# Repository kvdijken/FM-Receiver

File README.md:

# FM Receiver

In this project you will find my home built FM receiver. The goal is to create a receiver with discrete components only, no integrated circuits. It delivers line level audio. It only needs an additional audio amplifier to be able to hear your favorite radio station from the speakers.

Performance is very good. I receive all FM radio stations with great clarity. Its sensitivity is 11𝜇V.

It lets you dial into preprogrammed radio stations, or to select frequencies yourself. Also you can change some internal receiver parameters such as intermediate frequencies and lowside/highside injection. 

The user interface runs on an Arduino Nano 328P. The receiver itself is built off discrete parts, no integrated parts are used.

In this project you will find
* Arduino source code of the digital section (in folder 'firmware/FM Radio 5.8')
* Kicad project with the schematic and pcb layout of the analog section (in folder 'hardware')
* documentation (in folder 'documentation')
* a Python project to model differential pair amplifiers (in folder 'IF Amplifier')
* some photos of my implementation
* measurements I have done on this receiver (in folder 'measurements').

In this project you will not find the schematic for the digital section yet. I will still have to create this schematic. The digital section is not complicated however. It consists of an Arduino Nano, three pushbuttons, one LED, 1 rotary encoder, one display and one Adafruit Si5351 breakout board. From the Arduino sourcecode you should be able to discover the wiring. The Si5351 delivers the two local oscillator frequencies which are needed for the receiver.

Keep in mind that the schematic, and the pcb which is derived from the schematic contain an serious error. I kept this error in the schematic, to keep the schematic and pcb design in sync. The error is described in the documentation. Also is described how to work around the error, which is quite simple. You can still use the pcb design, even with this bug. In the next version of this receiver this error will be solved.

In the next few weeks, months, my main focus will be on measurements on the receiver. I will try to characterise the receiver as well as possible. From there the receiver can be improved.

On Youtube you can find a demonstration of this receiver: https://youtu.be/TlIiLwKdwg0

Current version is 1.0

Feel free to ask/contribute.

> Written with [StackEdit](https://stackedit.io/).

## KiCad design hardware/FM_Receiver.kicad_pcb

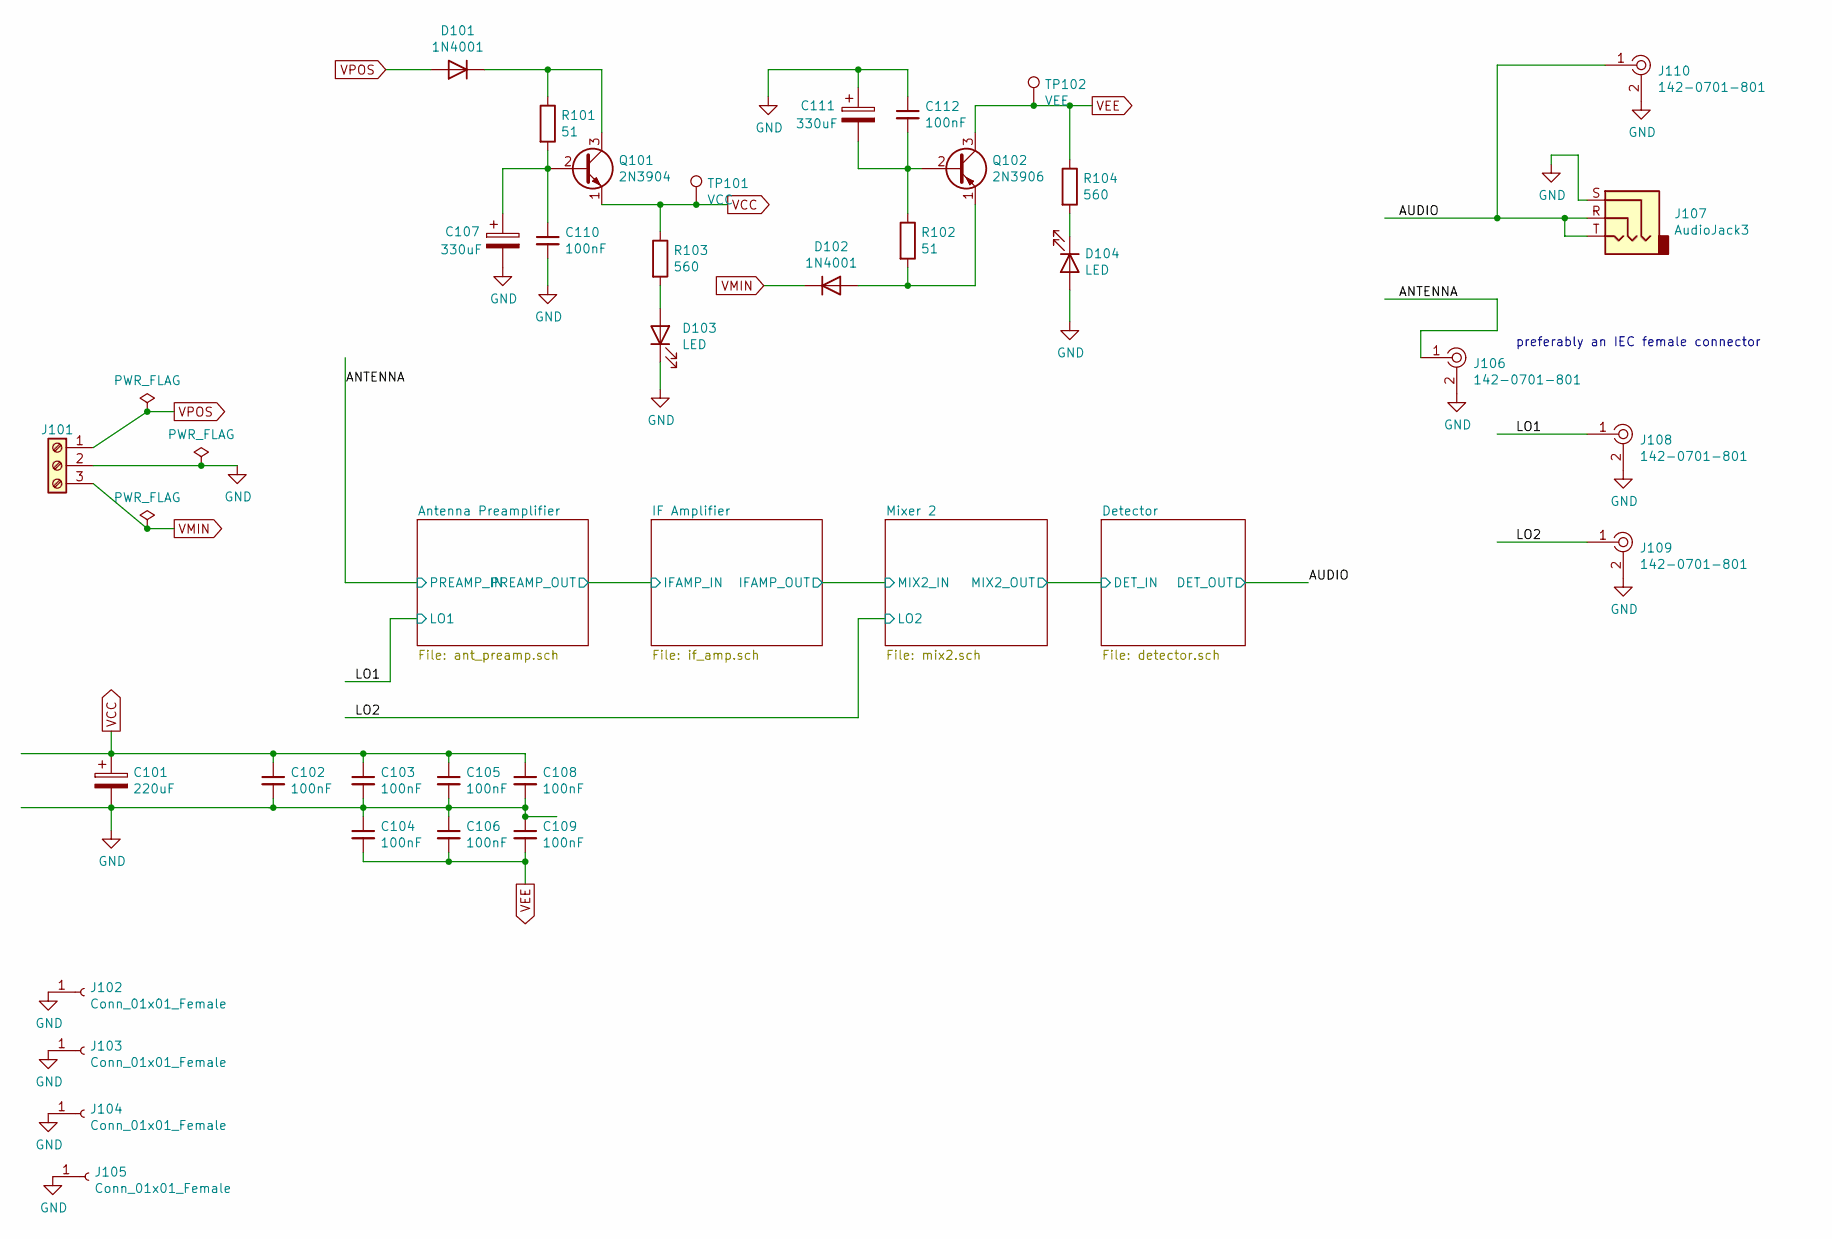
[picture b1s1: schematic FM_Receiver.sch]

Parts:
C101: 220uF; CP_Radial_D10.0mm_P5.00mm
C102, C103, C104, C105, C106, C108, C109, C110, C112: 100nF; C_Disc_D3.0mm_W2.0mm_P2.50mm
C107, C111: 330uF; CP_Radial_D10.0mm_P5.00mm
D101, D102: 1N4001; D_DO-41_SOD81_P7.62mm_Horizontal
D103, D104: LED; LED_D3.0mm
J101: Screw_Terminal_01x03; TerminalBlock_Phoenix_MPT-0,5-3-2.54_1x03_P2.54mm_Horizontal
J102, J103, J104, J105: Conn_01x01_Female; pad
J106, J108, J109, J110: 142-0701-801; SMA_Amphenol_901-144_Vertical; MPN 142-0701-801; Digi-Key_PN J502-ND
J107: AudioJack3; Jack_3.5mm_Ledino_KB3SPRS_Horizontal
Q101: 2N3904; TO-92_Inline
Q102: 2N3906; TO-92_Inline
R101, R102: 51; R_Axial_DIN0207_L6.3mm_D2.5mm_P10.16mm_Horizontal
R103, R104: 560; R_Axial_DIN0207_L6.3mm_D2.5mm_P10.16mm_Horizontal
TP101: VCC; TestPoint_Pad_D1.5mm
TP102: VEE; TestPoint_Pad_D1.5mm

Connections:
/ANTENNA: J106.1; also elsewhere on the board
/AUDIO: J107.R, J107.T, J110.1; also elsewhere on the board
/LO1: J108.1; also elsewhere on the board
/LO2: J109.1; also elsewhere on the board
GND: C101.2, C102.2, C103.2, C104.1, C105.2, C106.1, C107.2, C108.2, C109.1, C110.2, C111.1, C112.1, D103.1 (K), D104.2 (A), J101.2, J102.1, J103.1, J104.1, J105.1, J106.2, J107.S, J108.2, J109.2, J110.2; also elsewhere on the board
unnamed: C107.1, C110.1, Q101.2 (B), R101.2
unnamed: C111.2, C112.2, Q102.2 (B), R102.1
unnamed: D101.1 (K), Q101.3 (C), R101.1
unnamed: D102.2 (A), Q102.1 (E), R102.2
unnamed: D103.2 (A), R103.2
unnamed: D104.1 (K), R104.2
VCC: C101.1, C102.1, C103.1, C105.1, C108.1, Q101.1 (E), R103.1, TP101.1; also elsewhere on the board
VEE: C104.2, C106.2, C109.2, Q102.3 (C), R104.1, TP102.1; also elsewhere on the board
VMIN: D102.1 (K), J101.3
VPOS: D101.2 (A), J101.1

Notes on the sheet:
preferably an IEC female connector

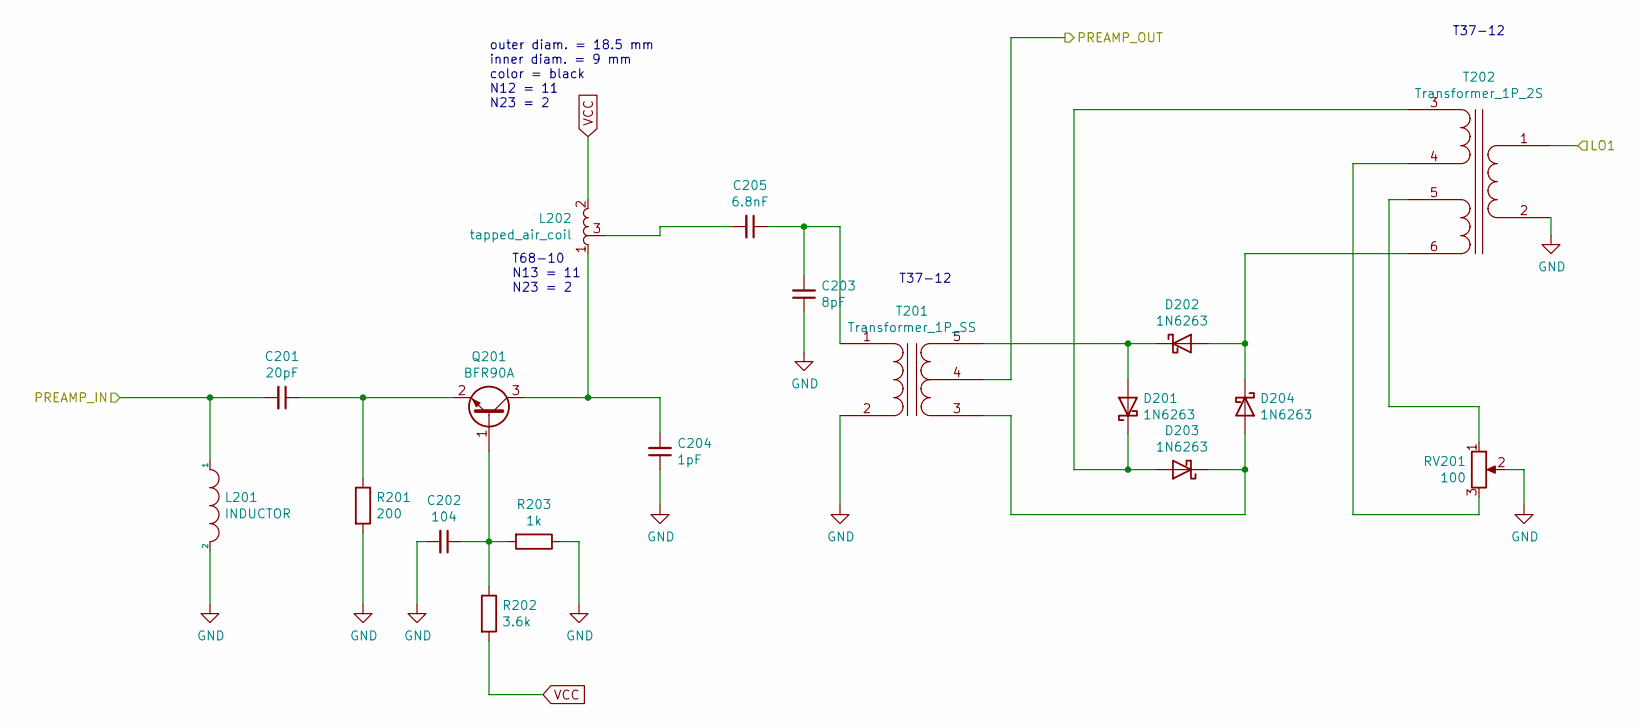
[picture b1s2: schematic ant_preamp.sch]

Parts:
C201: 20pF; C_Disc_D3.0mm_W2.0mm_P2.50mm
C202: 104; C_Disc_D3.0mm_W2.0mm_P2.50mm
C203: 8pF; C_Disc_D3.0mm_W2.0mm_P2.50mm
C204: 1pF; C_Disc_D3.0mm_W2.0mm_P2.50mm
C205: 6.8nF; C_Disc_D3.0mm_W2.0mm_P2.50mm
D201, D202, D203, D204: 1N6263; D_DO-35_SOD27_P7.62mm_Horizontal
L201: INDUCTOR; R_Axial_DIN0617_L17.0mm_D6.0mm_P20.32mm_Horizontal
L202: tapped_air_coil; tapped_coil
Q201: BFR90A; BFR90A_2
R201: 200; R_Axial_DIN0207_L6.3mm_D2.5mm_P10.16mm_Horizontal
R202: 3.6k; R_Axial_DIN0207_L6.3mm_D2.5mm_P10.16mm_Horizontal
R203: 1k; R_Axial_DIN0207_L6.3mm_D2.5mm_P10.16mm_Horizontal
RV201: 100; Potentiometer_Bourns_3266Y_Vertical
T201: Transformer_1P_SS; toroid_5_12
T202: Transformer_1P_2S; toroid_6_12

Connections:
/ANTENNA: C201.2, L201.1; also elsewhere on the board
/IF Amplifier/IFAMP_IN: T201.4 (SC); also elsewhere on the board
/LO1: T202.1 (AA); also elsewhere on the board
GND: C202.2, C203.1, C204.1, L201.2, R201.2, R203.1, RV201.2, T201.2 (AB), T202.2 (AB); also elsewhere on the board
unnamed: C201.1, Q201.2 (E), R201.1
unnamed: C202.1, Q201.1 (B), R202.1, R203.2
unnamed: C203.2, C205.1, T201.1 (AA)
unnamed: C204.2, L202.1, Q201.3 (C)
unnamed: C205.2, L202.3
unnamed: D201.1 (K), D203.2 (A), T202.3 (SA)
unnamed: D201.2 (A), D202.1 (K), T201.5 (SB)
unnamed: D202.2 (A), D204.1 (K), T202.6 (SD)
unnamed: D203.1 (K), D204.2 (A), T201.3 (SA)
unnamed: RV201.1, T202.5 (SC)
unnamed: RV201.3, T202.4 (SB)
VCC: L202.2, R202.2; also elsewhere on the board

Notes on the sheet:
outer diam. = 18.5 mm inner diam. = 9 mm color = black N12 = 11 N23 = 2
T37-12
T68-10 N13 = 11 N23 = 2

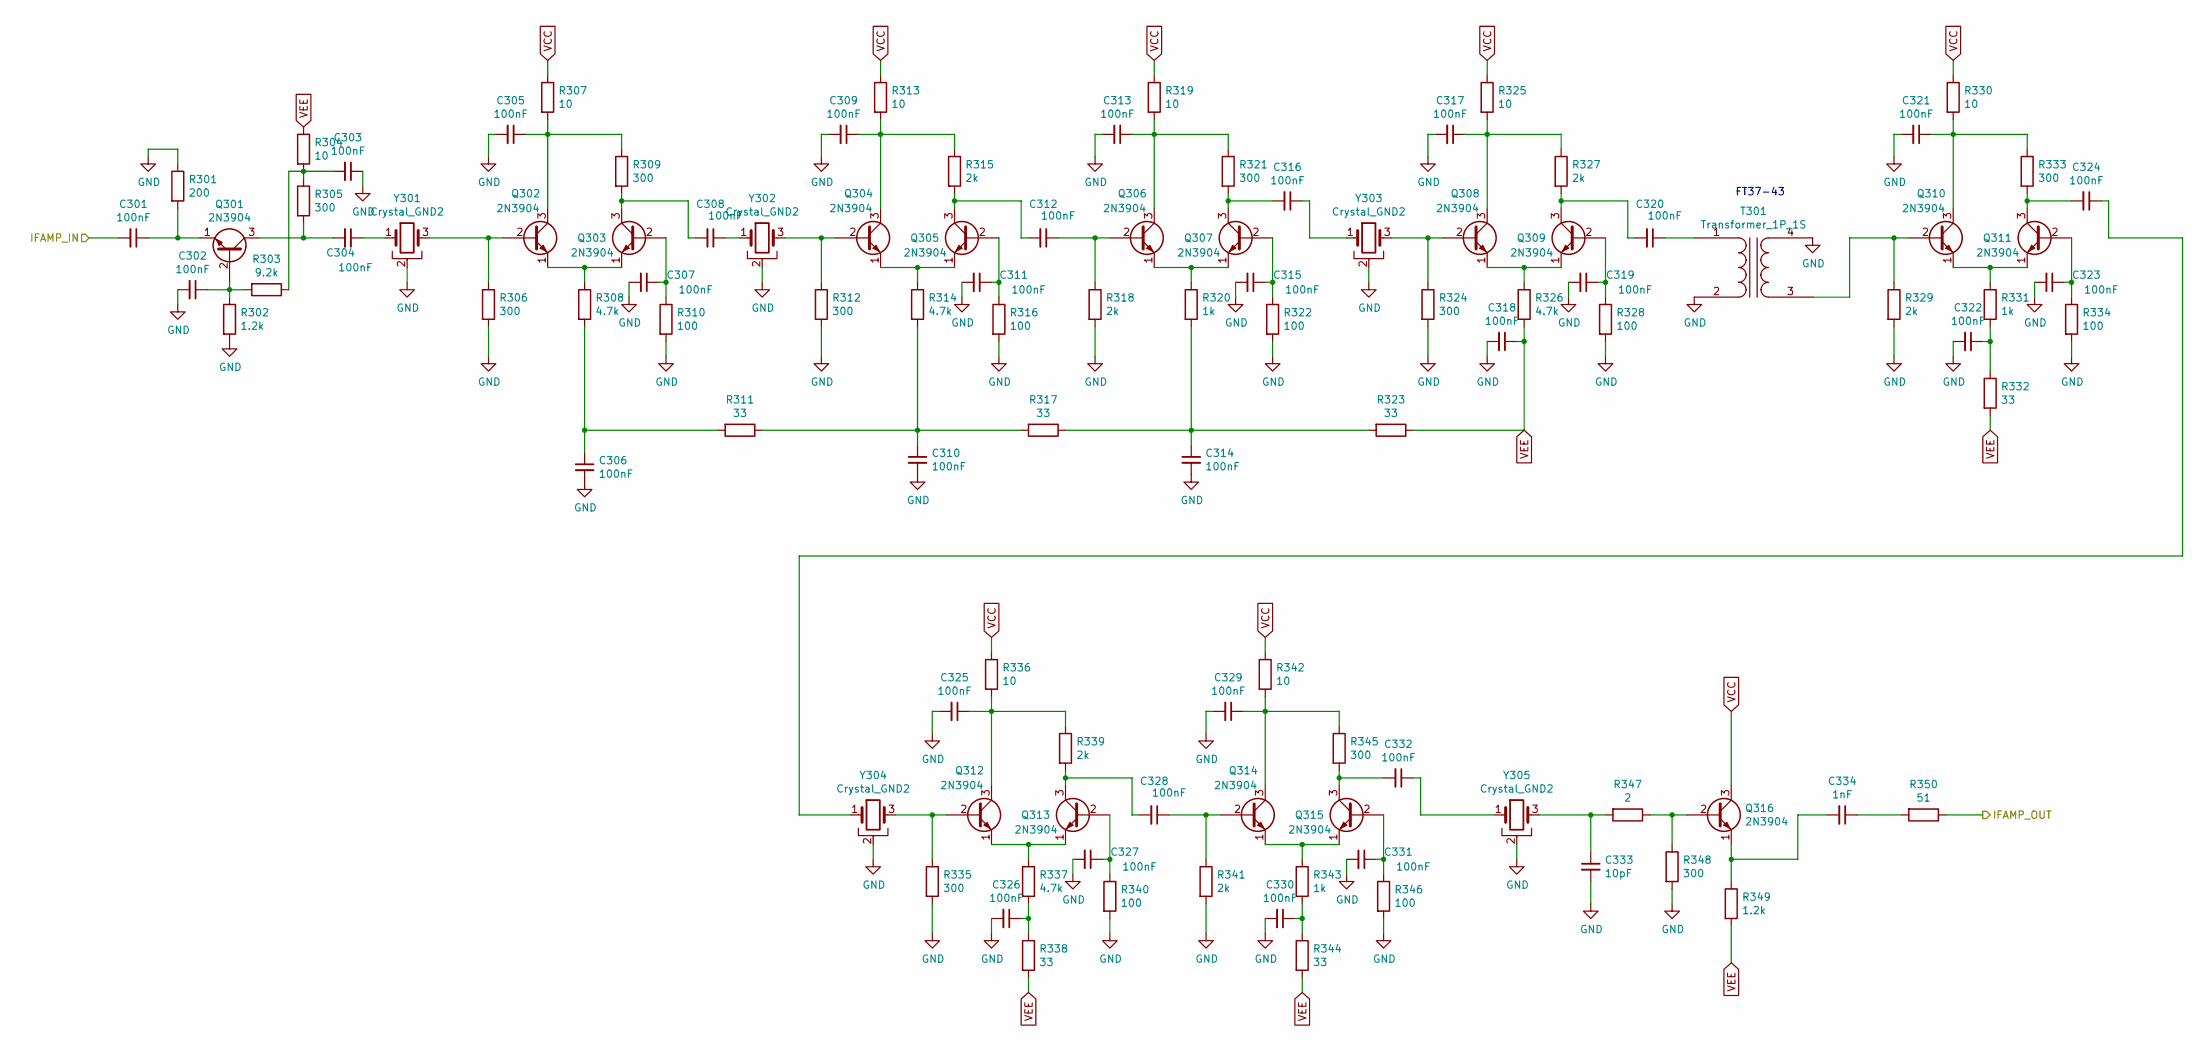
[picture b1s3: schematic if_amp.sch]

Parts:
C301, C302, C303, C304, C305, C306, C307, C308, C309, C310, C311, C312, C313, C314, C315, C316, C317, C318, C319, C320, C321, C322, C323, C324, C325, C326, C327, C328, C329, C330, C331, C332: 100nF; C_Disc_D3.0mm_W2.0mm_P2.50mm
C333: 10pF; C_Disc_D3.0mm_W2.0mm_P2.50mm
C334: 1nF; C_Disc_D3.0mm_W2.0mm_P2.50mm
Q301, Q302, Q303, Q304, Q305, Q306, Q307, Q308, Q309, Q310, Q311, Q312, Q313, Q314, Q315, Q316: 2N3904; TO-92_Inline
R301: 200; R_Axial_DIN0207_L6.3mm_D2.5mm_P10.16mm_Horizontal
R302, R349: 1.2k; R_Axial_DIN0207_L6.3mm_D2.5mm_P10.16mm_Horizontal
R303: 9.2k; R_Axial_DIN0207_L6.3mm_D2.5mm_P10.16mm_Horizontal
R304, R307, R313, R319, R325, R330, R336, R342: 10; R_Axial_DIN0207_L6.3mm_D2.5mm_P10.16mm_Horizontal
R305, R306, R309, R312, R321, R324, R333, R335, R345, R348: 300; R_Axial_DIN0207_L6.3mm_D2.5mm_P10.16mm_Horizontal
R308, R314, R326, R337: 4.7k; R_Axial_DIN0207_L6.3mm_D2.5mm_P10.16mm_Horizontal
R310, R316, R322, R328, R334, R340, R346: 100; R_Axial_DIN0207_L6.3mm_D2.5mm_P10.16mm_Horizontal
R311, R317, R323, R332, R338, R344: 33; R_Axial_DIN0207_L6.3mm_D2.5mm_P10.16mm_Horizontal
R315, R318, R327, R329, R339, R341: 2k; R_Axial_DIN0207_L6.3mm_D2.5mm_P10.16mm_Horizontal
R320, R331, R343: 1k; R_Axial_DIN0207_L6.3mm_D2.5mm_P10.16mm_Horizontal
R347: 2; R_Axial_DIN0207_L6.3mm_D2.5mm_P10.16mm_Horizontal
R350: 51; R_Axial_DIN0207_L6.3mm_D2.5mm_P10.16mm_Horizontal
T301: Transformer_1P_1S; toroid_4_10
Y301, Y302, Y303, Y304, Y305: Crystal_GND2; Resonator_muRata_CSTLSxxxG-3Pin_W8.0mm_H3.0mm

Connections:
/IF Amplifier/IFAMP_IN: C301.2; also elsewhere on the board
/IF Amplifier/IFAMP_OUT: R350.1; also elsewhere on the board
GND: C302.2, C303.1, C305.2, C306.2, C307.2, C309.2, C310.2, C311.2, C313.2, C314.2, C315.2, C317.2, C318.2, C319.2, C321.2, C322.2, C323.2, C325.2, C326.2, C327.2, C329.2, C330.2, C331.2, C333.2, R301.1, R302.2, R306.2, R310.2, R312.2, R316.2, R318.2, R322.2, R324.2, R328.2, R329.2, R334.2, R335.2, R340.2, R341.2, R346.2, R348.2, T301.2 (AB), T301.4 (SB), Y301.2, Y302.2, Y303.2, Y304.2, Y305.2; also elsewhere on the board
unnamed: C301.1, Q301.1 (E), R301.2
unnamed: C302.1, Q301.2 (B), R302.1, R303.2
unnamed: C303.2, R303.1, R304.2, R305.1
unnamed: C304.1, Y301.1
unnamed: C304.2, Q301.3 (C), R305.2
unnamed: C305.1, Q302.3 (C), R307.2, R309.1
unnamed: C306.1, R308.2, R311.2
unnamed: C307.1, Q303.2 (B), R310.1
unnamed: C308.1, Y302.1
unnamed: C308.2, Q303.3 (C), R309.2
unnamed: C309.1, Q304.3 (C), R313.2, R315.1
unnamed: C310.1, R311.1, R314.2, R317.2
unnamed: C311.1, Q305.2 (B), R316.1
unnamed: C312.1, Q306.2 (B), R318.1
unnamed: C312.2, Q305.3 (C), R315.2
unnamed: C313.1, Q306.3 (C), R319.2, R321.1
unnamed: C314.1, R317.1, R320.2, R323.2
unnamed: C315.1, Q307.2 (B), R322.1
unnamed: C316.1, Y303.1
unnamed: C316.2, Q307.3 (C), R321.2
unnamed: C317.1, Q308.3 (C), R325.2, R327.1
unnamed: C319.1, Q309.2 (B), R328.1
unnamed: C320.1, T301.1 (AA)
unnamed: C320.2, Q309.3 (C), R327.2
unnamed: C321.1, Q310.3 (C), R330.2, R333.1
unnamed: C322.1, R331.2, R332.1
unnamed: C323.1, Q311.2 (B), R334.1
unnamed: C324.1, Y304.1
unnamed: C324.2, Q311.3 (C), R333.2
unnamed: C325.1, Q312.3 (C), R336.2, R339.1
unnamed: C326.1, R337.2, R338.1
unnamed: C327.1, Q313.2 (B), R340.1
unnamed: C328.1, Q314.2 (B), R341.1
unnamed: C328.2, Q313.3 (C), R339.2
unnamed: C329.1, Q314.3 (C), R342.2, R345.1
unnamed: C330.1, R343.2, R344.1
unnamed: C331.1, Q315.2 (B), R346.1
unnamed: C332.1, Y305.1
unnamed: C332.2, Q315.3 (C), R345.2
unnamed: C333.1, R347.2, Y305.3
unnamed: C334.1, R350.2
unnamed: C334.2, Q316.1 (E), R349.1
unnamed: Q302.1 (E), Q303.1 (E), R308.1
unnamed: Q302.2 (B), R306.1, Y301.3
unnamed: Q304.1 (E), Q305.1 (E), R314.1
unnamed: Q304.2 (B), R312.1, Y302.3
unnamed: Q306.1 (E), Q307.1 (E), R320.1
unnamed: Q308.1 (E), Q309.1 (E), R326.1
unnamed: Q308.2 (B), R324.1, Y303.3
unnamed: Q310.1 (E), Q311.1 (E), R331.1
unnamed: Q310.2 (B), R329.1, T301.3 (SA)
unnamed: Q312.1 (E), Q313.1 (E), R337.1
unnamed: Q312.2 (B), R335.1, Y304.3
unnamed: Q314.1 (E), Q315.1 (E), R343.1
unnamed: Q316.2 (B), R347.1, R348.1
VCC: Q316.3 (C), R307.1, R313.1, R319.1, R325.1, R330.1, R336.1, R342.1; also elsewhere on the board
VEE: C318.1, R304.1, R323.1, R326.2, R332.2, R338.2, R344.2, R349.2; also elsewhere on the board

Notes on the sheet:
FT37-43

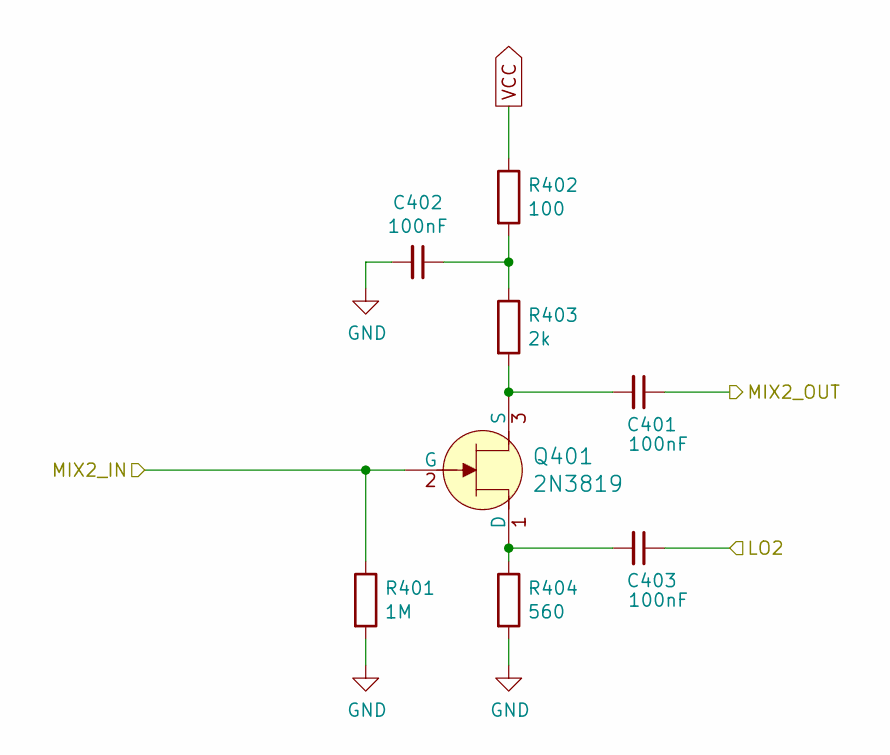
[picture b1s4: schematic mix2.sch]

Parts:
C401, C402, C403: 100nF; C_Disc_D3.0mm_W2.0mm_P2.50mm
Q401: 2N3819; TO-92-3; MPN 2N3819; Digi-Key_PN 2N3819CS-ND
R401: 1M; R_Axial_DIN0207_L6.3mm_D2.5mm_P10.16mm_Horizontal
R402: 100; R_Axial_DIN0207_L6.3mm_D2.5mm_P10.16mm_Horizontal
R403: 2k; R_Axial_DIN0207_L6.3mm_D2.5mm_P10.16mm_Horizontal
R404: 560; R_Axial_DIN0207_L6.3mm_D2.5mm_P10.16mm_Horizontal

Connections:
/Detector/DET_IN: C401.1; also elsewhere on the board
/IF Amplifier/IFAMP_OUT: Q401.2 (G), R401.1; also elsewhere on the board
/LO2: C403.1; also elsewhere on the board
GND: C402.2, R401.2, R404.2; also elsewhere on the board
unnamed: C401.2, Q401.3 (S), R403.2
unnamed: C402.1, R402.2, R403.1
unnamed: C403.2, Q401.1 (D), R404.1
VCC: R402.1; also elsewhere on the board

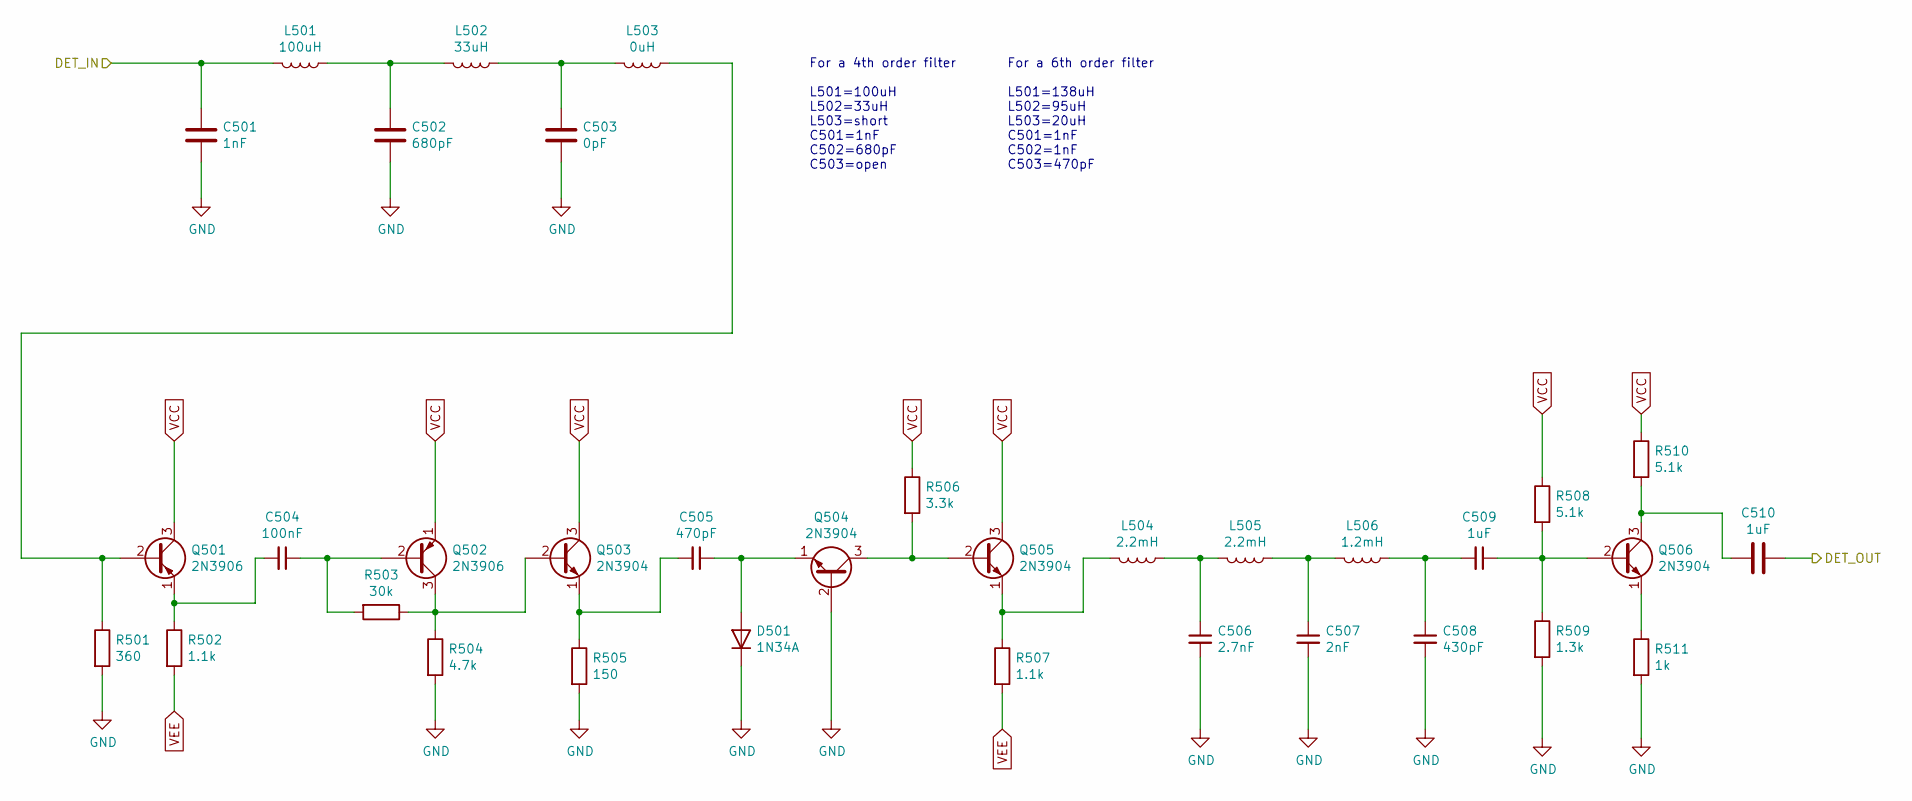
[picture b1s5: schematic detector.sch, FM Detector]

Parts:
C501: 1nF; C_Disc_D3.0mm_W2.0mm_P2.50mm
C502: 680pF; C_Disc_D3.0mm_W2.0mm_P2.50mm
C503: 0pF; C_Disc_D3.0mm_W2.0mm_P2.50mm
C504: 100nF; C_Disc_D3.0mm_W2.0mm_P2.50mm
C505: 470pF; C_Disc_D3.0mm_W2.0mm_P2.50mm
C506: 2.7nF; C_Disc_D3.0mm_W2.0mm_P2.50mm
C507: 2nF; C_Disc_D3.0mm_W2.0mm_P2.50mm
C508: 430pF; C_Disc_D3.0mm_W2.0mm_P2.50mm
C509, C510: 1uF; C_Rect_L10.3mm_W5.7mm_P7.50mm_MKS4
D501: 1N34A; D_DO-34_SOD68_P7.62mm_Horizontal
L501: 100uH; R_Axial_DIN0309_L9.0mm_D3.2mm_P12.70mm_Horizontal
L502: 33uH; R_Axial_DIN0309_L9.0mm_D3.2mm_P12.70mm_Horizontal
L503: 0uH; R_Axial_DIN0309_L9.0mm_D3.2mm_P12.70mm_Horizontal
L504, L505: 2.2mH; L_Radial_D8.7mm_P5.00mm_Fastron_07HCP
L506: 1.2mH; L_Radial_D8.7mm_P5.00mm_Fastron_07HCP
Q501, Q502: 2N3906; TO-92_Inline
Q503, Q504, Q505, Q506: 2N3904; TO-92_Inline
R501: 360; R_Axial_DIN0207_L6.3mm_D2.5mm_P10.16mm_Horizontal
R502, R507: 1.1k; R_Axial_DIN0207_L6.3mm_D2.5mm_P10.16mm_Horizontal
R503: 30k; R_Axial_DIN0207_L6.3mm_D2.5mm_P10.16mm_Horizontal
R504: 4.7k; R_Axial_DIN0207_L6.3mm_D2.5mm_P10.16mm_Horizontal
R505: 150; R_Axial_DIN0207_L6.3mm_D2.5mm_P10.16mm_Horizontal
R506: 3.3k; R_Axial_DIN0207_L6.3mm_D2.5mm_P10.16mm_Horizontal
R508, R510: 5.1k; R_Axial_DIN0207_L6.3mm_D2.5mm_P10.16mm_Horizontal
R509: 1.3k; R_Axial_DIN0207_L6.3mm_D2.5mm_P10.16mm_Horizontal
R511: 1k; R_Axial_DIN0207_L6.3mm_D2.5mm_P10.16mm_Horizontal

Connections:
/AUDIO: C510.1; also elsewhere on the board
/Detector/DET_IN: C501.1, L501.2; also elsewhere on the board
GND: C501.2, C502.2, C503.2, C506.2, C507.2, C508.2, D501.1 (K), Q504.2 (B), R501.2, R504.2, R505.2, R509.2, R511.2; also elsewhere on the board
unnamed: C502.1, L501.1, L502.2
unnamed: C503.1, L502.1, L503.2
unnamed: C504.1, Q502.2 (B), R503.2
unnamed: C504.2, Q501.1 (E), R502.1
unnamed: C505.1, D501.2 (A), Q504.1 (E)
unnamed: C505.2, Q503.1 (E), R505.1
unnamed: C506.1, L504.1, L505.2
unnamed: C507.1, L505.1, L506.2
unnamed: C508.1, C509.2, L506.1
unnamed: C509.1, Q506.2 (B), R508.2, R509.1
unnamed: C510.2, Q506.3 (C), R510.2
unnamed: L503.1, Q501.2 (B), R501.1
unnamed: L504.2, Q505.1 (E), R507.1
unnamed: Q502.3 (C), Q503.2 (B), R503.1, R504.1
unnamed: Q504.3 (C), Q505.2 (B), R506.2
unnamed: Q506.1 (E), R511.1
VCC: Q501.3 (C), Q502.1 (E), Q503.3 (C), Q505.3 (C), R506.1, R508.1, R510.1; also elsewhere on the board
VEE: R502.2, R507.2; also elsewhere on the board

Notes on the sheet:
For a 4th order filter L501=100uH L502=33uH L503=short C501=1nF C502=680pF C503=open
For a 6th order filter L501=138uH L502=95uH L503=20uH C501=1nF C502=1nF C503=470pF

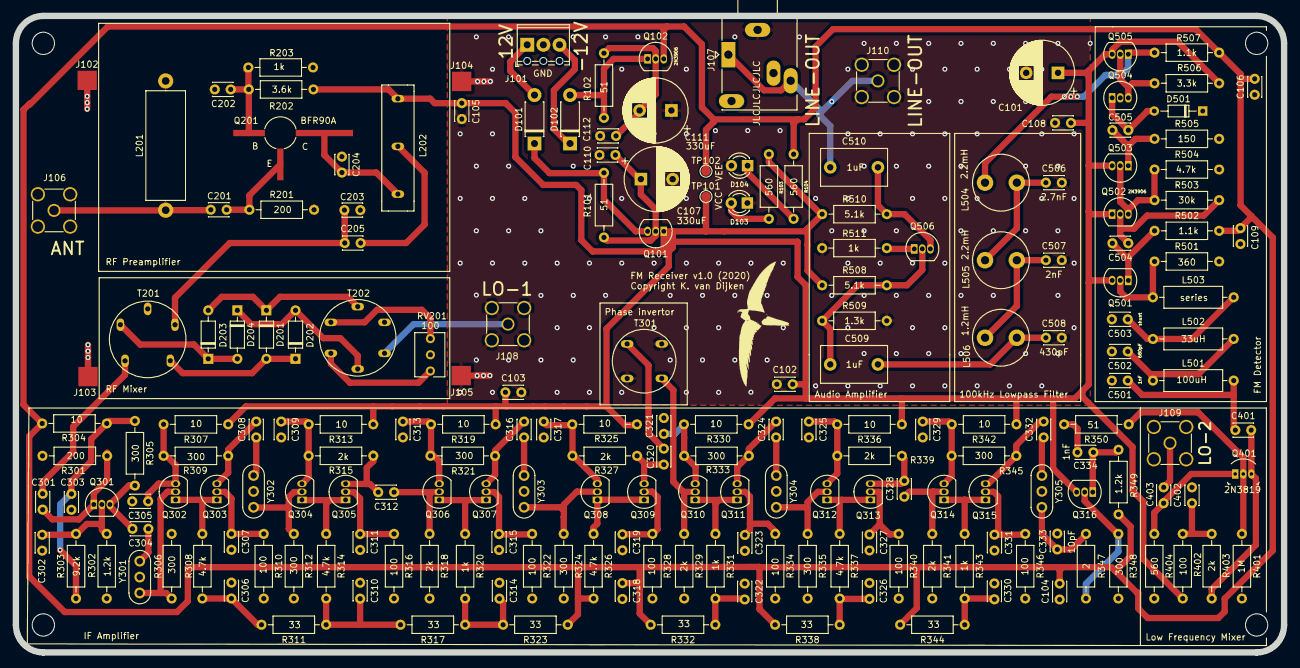
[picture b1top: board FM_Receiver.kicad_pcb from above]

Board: 2 copper layers, 199.4 x 100.1 mm, 200 parts (0 on the bottom side), 103 nets.

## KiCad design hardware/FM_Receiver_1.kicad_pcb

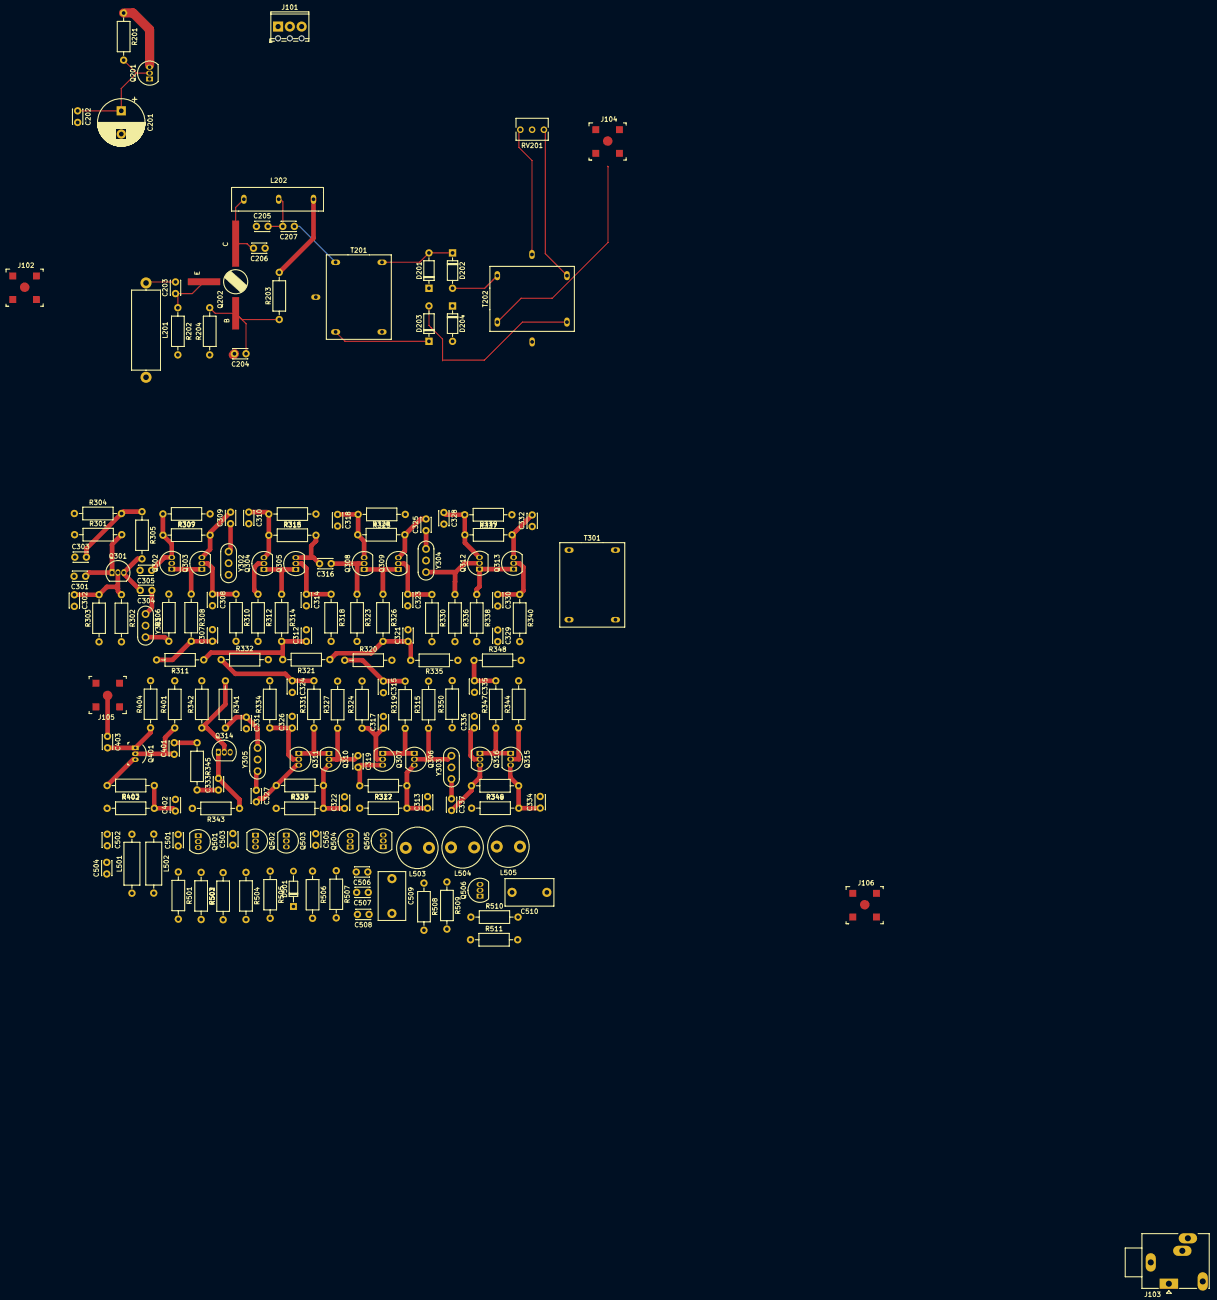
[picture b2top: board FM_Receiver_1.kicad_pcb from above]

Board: 2 copper layers, 175 parts (0 on the bottom side), 97 nets.

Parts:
C201: 330uF; CP_Radial_D10.0mm_P5.00mm
C202, C301, C302, C303, C304, C305, C307, C308, C309, C310, C312, C313, C314, C315, C316, C317, C318, C319, C321, C322, C323, C324, C325, C326, C327, C328, C329, C330, C331, C332, C333, C334, C335, C336, C337, C401, C402, C403, C501, C503: 100nF; C_Disc_D3.0mm_W2.0mm_P2.50mm
C203: 20pF; C_Disc_D3.0mm_W2.0mm_P2.50mm
C204: 104; C_Disc_D3.0mm_W2.0mm_P2.50mm
C205: 8pF; C_Disc_D3.0mm_W2.0mm_P2.50mm
C206: 1pF; C_Disc_D3.0mm_W2.0mm_P2.50mm
C207: 6.8nF; C_Disc_D3.0mm_W2.0mm_P2.50mm
C502: 1nF; C_Disc_D3.0mm_W2.0mm_P2.50mm
C504: 680pF; C_Disc_D3.0mm_W2.0mm_P2.50mm
C505: 470pF; C_Disc_D3.0mm_W2.0mm_P2.50mm
C506: 2.7nF; C_Disc_D3.0mm_W2.0mm_P2.50mm
C507: 2nF; C_Disc_D3.0mm_W2.0mm_P2.50mm
C508: 430pF; C_Disc_D3.0mm_W2.0mm_P2.50mm
C509, C510: 1uF; C_Rect_L10.3mm_W5.7mm_P7.50mm_MKS4
D201, D202, D203, D204: 1N6263; D_DO-35_SOD27_P7.62mm_Horizontal
D501: 1N34A; D_DO-34_SOD68_P7.62mm_Horizontal
J101: Screw_Terminal_01x03; TerminalBlock_Phoenix_MPT-0,5-3-2.54_1x03_P2.54mm_Horizontal
J102, J104, J105, J106: CONSMA001-SMD-G; RF_SMA_Receptical_Vertical_CONSMA001-SMD-G
J103: AudioJack3; Jack_3.5mm_Ledino_KB3SPRS_Horizontal
L201: INDUCTOR; R_Axial_DIN0617_L17.0mm_D6.0mm_P20.32mm_Horizontal
L202: tapped_air_coil; tapped_coil
L501: 100uH; R_Axial_DIN0309_L9.0mm_D3.2mm_P12.70mm_Horizontal
L502: 33uH; R_Axial_DIN0309_L9.0mm_D3.2mm_P12.70mm_Horizontal
L503, L504: 2.2mH; L_Radial_D8.7mm_P5.00mm_Fastron_07HCP
L505: 1.2mH; L_Radial_D8.7mm_P5.00mm_Fastron_07HCP
Q201, Q301, Q302, Q303, Q304, Q305, Q306, Q307, Q308, Q309, Q310, Q311, Q312, Q313, Q314, Q315, Q316, Q503, Q504, Q505, Q506: 2N3904; TO-92_Inline
Q202: BFR90A; BFR90A_1
Q401: 2N3819_NonStock; TO-92-3
Q501, Q502: 2N3906; TO-92_Inline
R201, R316, R322, R323, R327, R339, R344, R403: 2k; R_Axial_DIN0207_L6.3mm_D2.5mm_P10.16mm_Horizontal
R202, R302, R303: R; R_Axial_DIN0207_L6.3mm_D2.5mm_P10.16mm_Horizontal
R203: 3.6k; R_Axial_DIN0207_L6.3mm_D2.5mm_P10.16mm_Horizontal
R204, R326, R331, R347, R511: 1k; R_Axial_DIN0207_L6.3mm_D2.5mm_P10.16mm_Horizontal
R301: 200; R_Axial_DIN0207_L6.3mm_D2.5mm_P10.16mm_Horizontal
R304, R307, R313, R317, R325, R329, R337, R346: 10; R_Axial_DIN0207_L6.3mm_D2.5mm_P10.16mm_Horizontal
R305, R306, R309, R312, R315, R328, R333, R336, R342, R349: 300; R_Axial_DIN0207_L6.3mm_D2.5mm_P10.16mm_Horizontal
R308, R314, R319, R338, R504: 4.7k; R_Axial_DIN0207_L6.3mm_D2.5mm_P10.16mm_Horizontal
R310, R318, R324, R330, R334, R340, R350, R402: 100; R_Axial_DIN0207_L6.3mm_D2.5mm_P10.16mm_Horizontal
R311, R320, R321, R332, R335, R348: 33; R_Axial_DIN0207_L6.3mm_D2.5mm_P10.16mm_Horizontal
R341: 2; R_Axial_DIN0207_L6.3mm_D2.5mm_P10.16mm_Horizontal
R343: 1.2k; R_Axial_DIN0207_L6.3mm_D2.5mm_P10.16mm_Horizontal
R345: 51; R_Axial_DIN0207_L6.3mm_D2.5mm_P10.16mm_Horizontal
R401: 1M; R_Axial_DIN0207_L6.3mm_D2.5mm_P10.16mm_Horizontal
R404: 220; R_Axial_DIN0207_L6.3mm_D2.5mm_P10.16mm_Horizontal
R501: 360; R_Axial_DIN0207_L6.3mm_D2.5mm_P10.16mm_Horizontal
R502, R507: 1.1k; R_Axial_DIN0207_L6.3mm_D2.5mm_P10.16mm_Horizontal
R503: 30k; R_Axial_DIN0207_L6.3mm_D2.5mm_P10.16mm_Horizontal
R505: 150; R_Axial_DIN0207_L6.3mm_D2.5mm_P10.16mm_Horizontal
R506: 3.3k; R_Axial_DIN0207_L6.3mm_D2.5mm_P10.16mm_Horizontal
R508, R510: 5.1k; R_Axial_DIN0207_L6.3mm_D2.5mm_P10.16mm_Horizontal
R509: 1.3k; R_Axial_DIN0207_L6.3mm_D2.5mm_P10.16mm_Horizontal
RV201: 100; Potentiometer_Bourns_3266Y_Vertical
T201: Transformer_1P_SS; toroid_5
T202: Transformer_1P_2S; toroid_6
T301: Transformer_1P_1S; toroid_4
Y301, Y302, Y303, Y304, Y305: Crystal_GND2; Resonator_muRata_CSTLSxxxG-3Pin_W8.0mm_H3.0mm

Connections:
/ANTENNA: C203.2, J102.2, L201.1
/AUDIO: C510.1, J103.R, J103.T, J106.2
/Antenna Preamplifier/VCC2: L202.2, Q201.1, R203.2
/Detector/DET_IN: C502.1, L501.2, Q401.3, R403.2
/IF Amplifier/IFAMP_IN: C301.2, T201.4
/IF Amplifier/IFAMP_OUT: C401.2, R345.1
/LO1: J104.2, T202.1
/LO2: C403.1, J105.2
GND: C201.2, C202.2, C204.2, C205.1, C206.1, C302.2, C303.1, C305.2, C307.2, C308.2, C310.2, C312.2, C313.2, C314.2, C315.2, C317.2, C318.2, C321.2, C322.2, C323.2, C324.2, C326.2, C328.2, C329.2, C330.2, C331.2, C334.2, C335.2, C336.2, C402.2, C502.2, C504.2, C506.2, C507.2, C508.2, D501.1, J101.2, J102.1, J103.S, J104.1, J105.1, J106.1, L201.2, Q504.2, R202.2, R204.1, R301.1, R302.2, R306.2, R310.2, R312.2, R315.2, R318.2, R323.2, R324.2, R327.2, R330.2, R334.2, R336.2, R340.2, R342.2, R344.2, R350.2, R401.2, R404.2, R501.2, R504.2, R505.2, R509.2, R511.2, RV201.2, T201.2, T202.2, T301.2, T301.4, Y301.2, Y302.2, Y303.2, Y304.2, Y305.2
unnamed: C201.1, C202.1, Q201.2, R201.2
unnamed: C203.1, Q202.2, R202.1
unnamed: C204.1, Q202.1, R203.1, R204.2
unnamed: C205.2, C207.2, L202.3
unnamed: C206.2, L202.1, Q202.3
unnamed: C207.1, T201.1
unnamed: C301.1, Q301.1, R301.2
unnamed: C302.1, Q301.2, R302.1, R303.2
unnamed: C303.2, R304.2, R305.1
unnamed: C304.1, Y301.1
unnamed: C304.2, Q301.3, R305.2
unnamed: C305.1, Q302.3, R307.2, R309.1
unnamed: C307.1, R308.2, R311.2
unnamed: C308.1, Q303.2, R310.1
unnamed: C309.1, Y302.1
unnamed: C309.2, Q303.3, R309.2
unnamed: C310.1, Q304.3, R313.2, R316.1
unnamed: C312.1, R311.1, R314.2, R321.2
unnamed: C313.1, Q306.3, R317.2, R322.1
unnamed: C314.1, Q305.2, R318.1
unnamed: C315.1, R319.2, R320.1
unnamed: C316.1, Q308.2, R323.1
unnamed: C316.2, Q305.3, R316.2
unnamed: C317.1, Q307.2, R324.1
unnamed: C318.1, Q308.3, R325.2, R328.1
unnamed: C319.1, Q310.2, R327.1
unnamed: C319.2, Q307.3, R322.2
unnamed: C321.1, R321.1, R326.2, R335.2
unnamed: C322.1, Q310.3, R329.2, R333.1
unnamed: C323.1, Q309.2, R330.1
unnamed: C324.1, R331.2, R332.1
unnamed: C325.1, Y304.1
unnamed: C325.2, Q309.3, R328.2
unnamed: C326.1, Q311.2, R334.1
unnamed: C327.1, Y305.1
unnamed: C327.2, Q311.3, R333.2
unnamed: C328.1, Q312.3, R337.2, R339.1
unnamed: C330.1, Q313.2, R340.1
unnamed: C331.1, R341.2, Y305.3
unnamed: C332.1, T301.1
unnamed: C332.2, Q313.3, R339.2
unnamed: C333.1, R345.2
unnamed: C333.2, Q314.1, R343.1
unnamed: C334.1, Q315.3, R346.2, R349.1
unnamed: C335.1, R347.2, R348.1
unnamed: C336.1, Q316.2, R350.1
unnamed: C337.1, Y303.1
unnamed: C337.2, Q316.3, R349.2
unnamed: C401.1, Q401.2, R401.1
unnamed: C402.1, R402.2, R403.1
unnamed: C403.2, Q401.1, R404.1
unnamed: C501.1, Q501.2, R501.1
unnamed: C501.2, L502.1
unnamed: C503.1, Q502.2, R503.2
unnamed: C503.2, Q501.1, R502.1
unnamed: C504.1, L501.1, L502.2
unnamed: C505.1, D501.2, Q504.1
unnamed: C505.2, Q503.1, R505.1
unnamed: C506.1, L503.1, L504.2
unnamed: C507.1, L504.1, L505.2
unnamed: C508.1, C509.2, L505.1
unnamed: C509.1, Q506.2, R508.2, R509.1
unnamed: C510.2, Q506.3, R510.2
unnamed: D201.1, D203.2, T202.3
unnamed: D201.2, D202.1, T201.5
unnamed: D202.2, D204.1, T202.6
unnamed: D203.1, D204.2, T201.3
unnamed: L503.2, Q505.1, R507.1
unnamed: Q302.1, Q303.1, R308.1
unnamed: Q302.2, R306.1, Y301.3
unnamed: Q304.1, Q305.1, R314.1
unnamed: Q304.2, R312.1, Y302.3
unnamed: Q306.1, Q307.1, R319.1
unnamed: Q306.2, R315.1, Y303.3
unnamed: Q308.1, Q309.1, R326.1
unnamed: Q310.1, Q311.1, R331.1
unnamed: Q312.1, Q313.1, R338.1
unnamed: Q312.2, R336.1, Y304.3
unnamed: Q314.2, R341.1, R342.1
unnamed: Q315.1, Q316.1, R347.1
unnamed: Q315.2, R344.1, T301.3
unnamed: Q502.3, Q503.2, R503.1, R504.1
unnamed: Q504.3, Q505.2, R506.2
unnamed: Q506.1, R511.1
unnamed: RV201.1, T202.5
unnamed: RV201.3, T202.4
VCC: J101.1, Q201.3, Q314.3, Q501.3, Q502.1, Q503.3, Q505.3, R201.1, R307.1, R313.1, R317.1, R325.1, R329.1, R337.1, R346.1, R402.1, R506.1, R508.1, R510.1
VEE: C329.1, J101.3, R303.1, R304.1, R320.2, R332.2, R335.1, R338.2, R343.2, R348.2, R502.2, R507.2

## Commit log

2020-12-06 FM Receiver
    A receiver for FM radio reception.
2020-12-06 initial commit
    initial commit
2020-12-06 Create Diffpair4
    Create Diffpair4
2020-12-12 sensitivity measurement correction
2020-12-15 Initial commit
    Power Measurements

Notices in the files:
hardware/FM_Receiver.kicad_pcb:
Copyright K. van Dijken
